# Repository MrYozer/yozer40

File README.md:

# yozer40
A 40% split space keyboard

Kicad design files, firmware coming later

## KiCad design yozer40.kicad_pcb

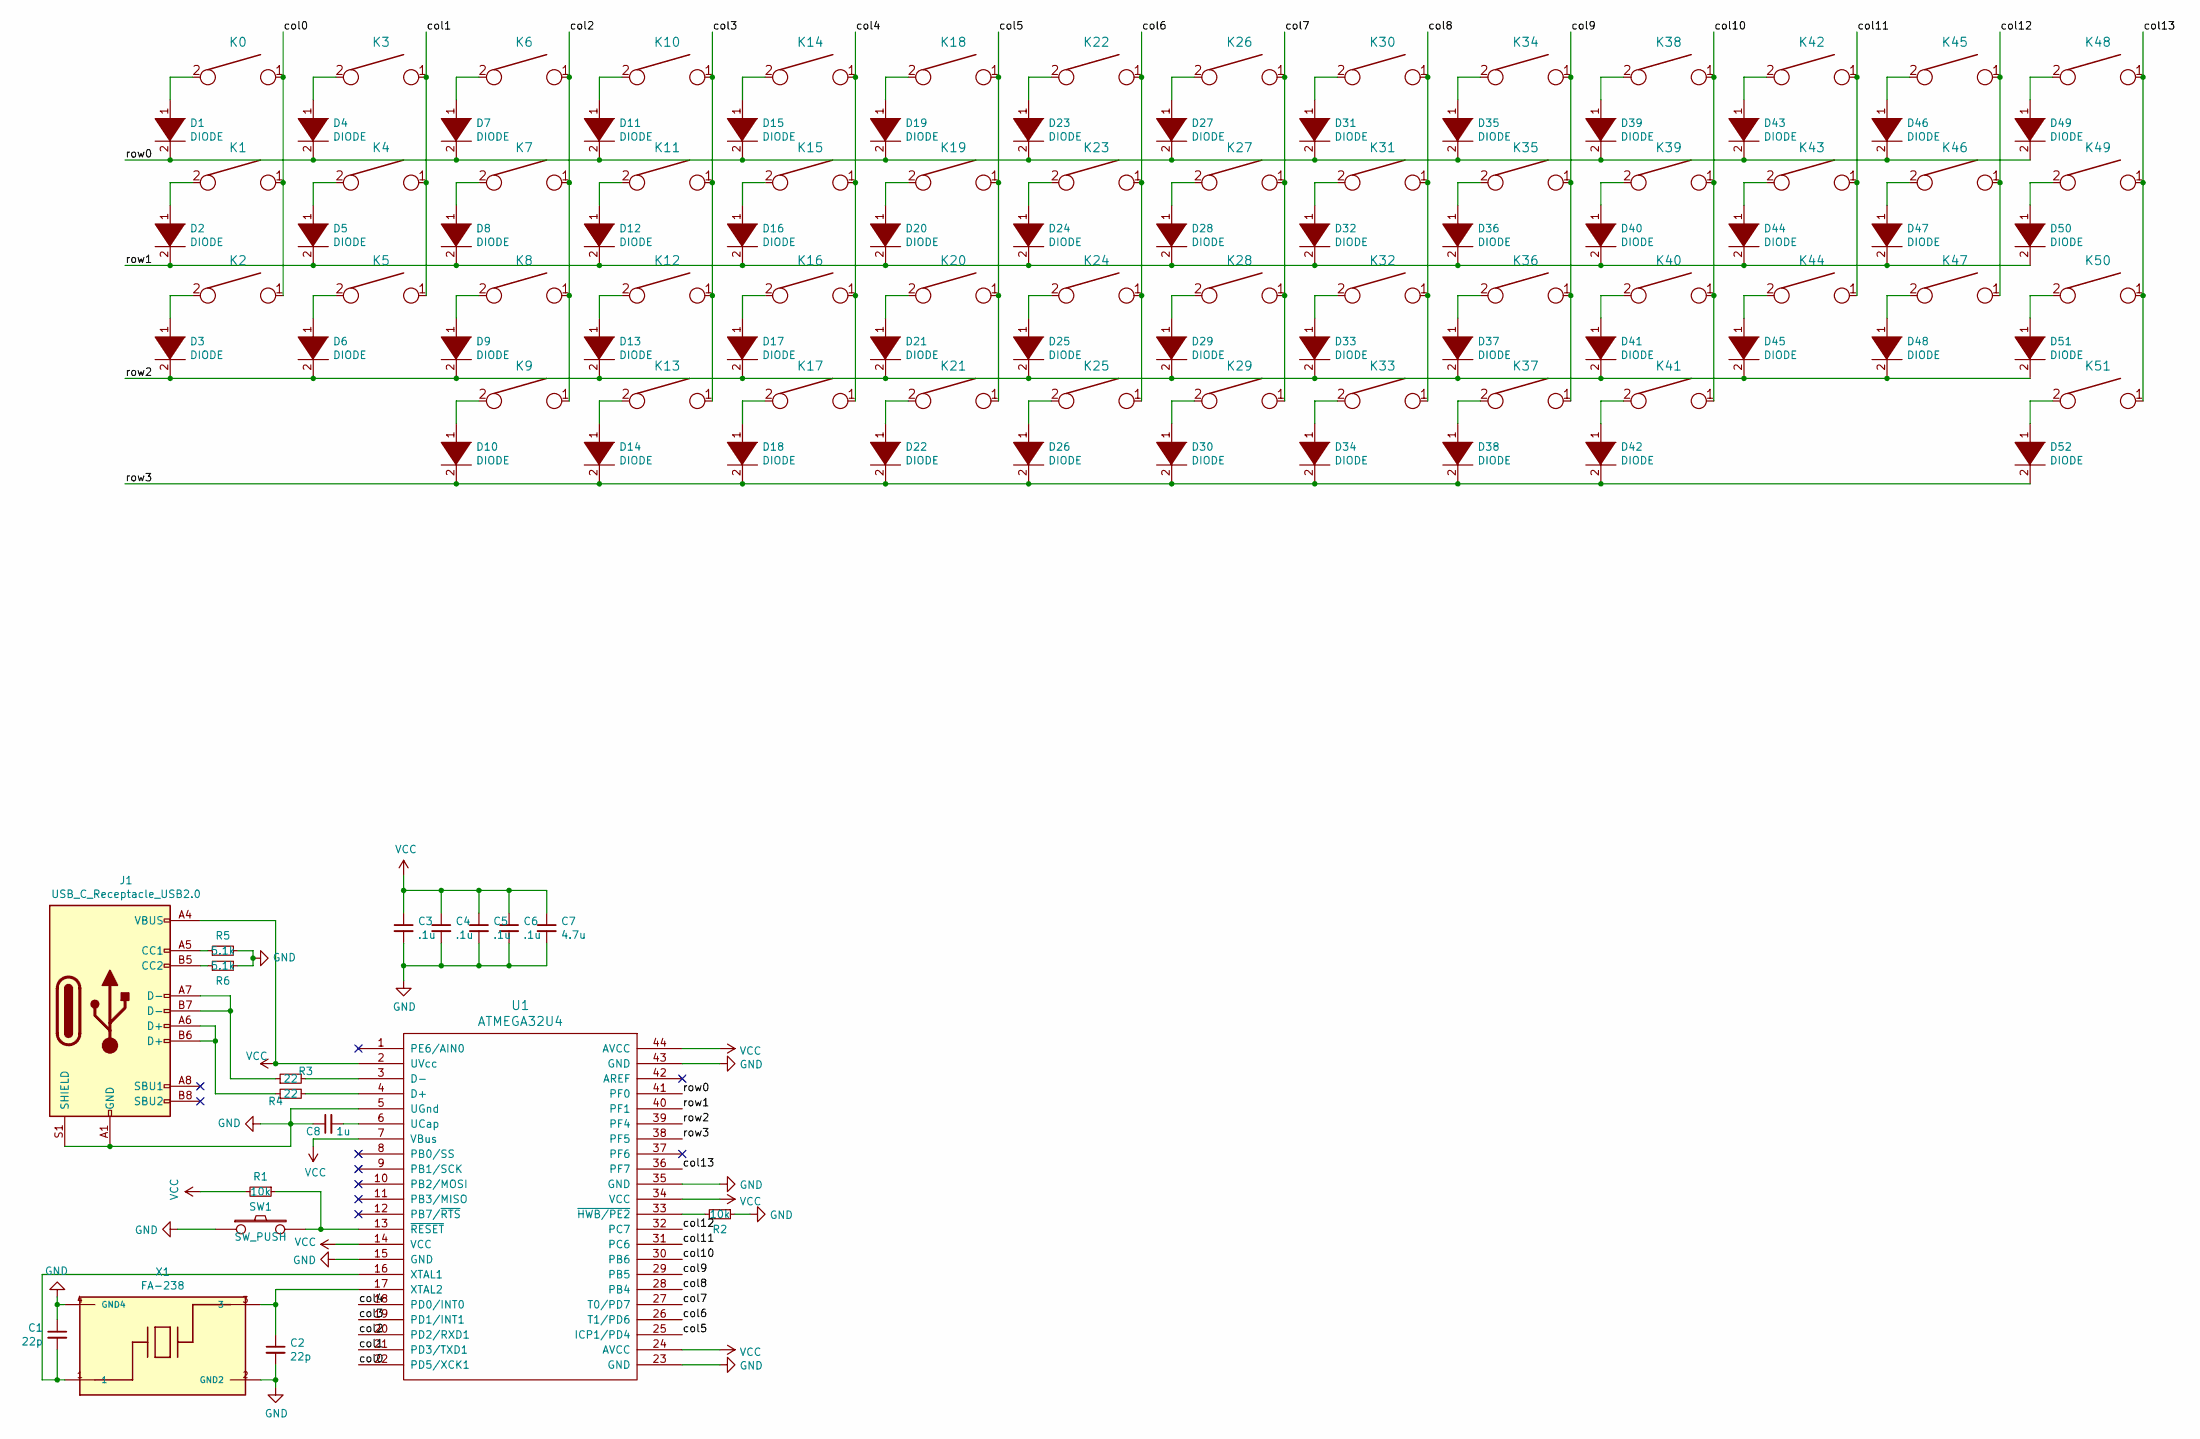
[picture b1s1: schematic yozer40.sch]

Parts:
C1, C2: 22p; C_0805_2012Metric_Pad1.18x1.45mm_HandSolder
C3, C4, C5, C6: .1u; C_0805_2012Metric_Pad1.18x1.45mm_HandSolder
C7: 4.7u; C_0805_2012Metric_Pad1.18x1.45mm_HandSolder
C8: 1u; C_0805_2012Metric_Pad1.18x1.45mm_HandSolder
D1, D2, D3, D4, D5, D6, D7, D8, D9, D10, D11, D12, D13, D14, D15, D16, D17, D18, D19, D20, D21, D22, D23, D24, D25, D26, D27, D28, D29, D30, D31, D32, D33, D34, D35, D36, D37, D38, D39, D40, D41, D42, D43, D44, D45, D46, D47, D48, D49, D50, D51, D52: DIODE; D_0805_2012Metric_Pad1.15x1.40mm_HandSolder
J1: USB_C_Receptacle_USB2.0; USB_C_Receptacle_GCT_USB4085
K0, K1, K2, K3, K6, K7, K8, K9, K10, K11, K12, K13, K14, K15, K16, K17, K18, K19, K20, K22, K23, K24, K25, K26, K27, K28, K30, K31, K32, K33, K34, K35, K36, K37, K38, K39, K40, K41, K42, K43, K44, K45, K46, K48, K50, K51: KEYSW; SW_Cherry_MX_1.00u_PCB
K4, K21, K29, K47: KEYSW; SW_Cherry_MX_1.25u_PCB
K5, K49: KEYSW; SW_Cherry_MX_1.75u_PCB
R1, R2: 10k; R_0805_2012Metric_Pad1.20x1.40mm_HandSolder
R3, R4: 22; R_0805_2012Metric_Pad1.20x1.40mm_HandSolder
R5, R6: 5.1k; R_0805_2012Metric_Pad1.20x1.40mm_HandSolder
SW1: SW_PUSH; SW_SPST_TL3342
U1: ATMEGA32U4; TQFP-44_10x10mm_P0.8mm
X1: FA-238; OSCCC320X250X70-4N

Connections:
/col0: K0.1, K1.1, K2.1, U1.22 (PD5/XCK1)
/col1: K3.1, K4.1, K5.1, U1.21 (PD3/TXD1)
/col2: K6.1, K7.1, K8.1, K9.1, U1.20 (PD2/RXD1)
/col3: K10.1, K11.1, K12.1, K13.1, U1.19 (PD1/INT1)
/col4: K14.1, K15.1, K16.1, K17.1, U1.18 (PD0/INT0)
/col5: K18.1, K19.1, K20.1, K21.1, U1.25 (ICP1/PD4)
/col6: K22.1, K23.1, K24.1, K25.1, U1.26 (T1/PD6)
/col7: K26.1, K27.1, K28.1, K29.1, U1.27 (T0/PD7)
/col8: K30.1, K31.1, K32.1, K33.1, U1.28 (PB4)
/col9: K34.1, K35.1, K36.1, K37.1, U1.29 (PB5)
/col10: K38.1, K39.1, K40.1, K41.1, U1.30 (PB6)
/col11: K42.1, K43.1, K44.1, U1.31 (PC6)
/col12: K45.1, K46.1, K47.1, U1.32 (PC7)
/col13: K48.1, K49.1, K50.1, K51.1, U1.36 (PF7)
/row0: D1.2 (A), D4.2 (A), D7.2 (A), D11.2 (A), D15.2 (A), D19.2 (A), D23.2 (A), D27.2 (A), D31.2 (A), D35.2 (A), D39.2 (A), D43.2 (A), D46.2 (A), D49.2 (A), U1.41 (PF0)
/row1: D2.2 (A), D5.2 (A), D8.2 (A), D12.2 (A), D16.2 (A), D20.2 (A), D24.2 (A), D28.2 (A), D32.2 (A), D36.2 (A), D40.2 (A), D44.2 (A), D47.2 (A), D50.2 (A), U1.40 (PF1)
/row2: D3.2 (A), D6.2 (A), D9.2 (A), D13.2 (A), D17.2 (A), D21.2 (A), D25.2 (A), D29.2 (A), D33.2 (A), D37.2 (A), D41.2 (A), D45.2 (A), D48.2 (A), D51.2 (A), U1.39 (PF4)
/row3: D10.2 (A), D14.2 (A), D18.2 (A), D22.2 (A), D26.2 (A), D30.2 (A), D34.2 (A), D38.2 (A), D42.2 (A), D52.2 (A), U1.38 (PF5)
GND: C1.1, C2.2, C3.2, C4.2, C5.2, C6.2, C7.2, C8.1, J1.A1 (GND), J1.A12 (GND), J1.B1 (GND), J1.B12 (GND), J1.S1 (SHIELD), R2.1, R5.2, R6.2, SW1.1, U1.5 (UGnd), U1.15 (GND), U1.23 (GND), U1.35 (GND), U1.43 (GND), X1.2 (GND2), X1.4 (GND4)
unnamed: C1.2, U1.16 (XTAL1), X1.1
unnamed: C2.1, U1.17 (XTAL2), X1.3
unnamed: C8.2, U1.6 (UCap)
unnamed: D1.1 (K), K0.2
unnamed: D2.1 (K), K1.2
unnamed: D3.1 (K), K2.2
unnamed: D4.1 (K), K3.2
unnamed: D5.1 (K), K4.2
unnamed: D6.1 (K), K5.2
unnamed: D7.1 (K), K6.2
unnamed: D8.1 (K), K7.2
unnamed: D9.1 (K), K8.2
unnamed: D10.1 (K), K9.2
unnamed: D11.1 (K), K10.2
unnamed: D12.1 (K), K11.2
unnamed: D13.1 (K), K12.2
unnamed: D14.1 (K), K13.2
unnamed: D15.1 (K), K14.2
unnamed: D16.1 (K), K15.2
unnamed: D17.1 (K), K16.2
unnamed: D18.1 (K), K17.2
unnamed: D19.1 (K), K18.2
unnamed: D20.1 (K), K19.2
unnamed: D21.1 (K), K20.2
unnamed: D22.1 (K), K21.2
unnamed: D23.1 (K), K22.2
unnamed: D24.1 (K), K23.2
unnamed: D25.1 (K), K24.2
unnamed: D26.1 (K), K25.2
unnamed: D27.1 (K), K26.2
unnamed: D28.1 (K), K27.2
unnamed: D29.1 (K), K28.2
unnamed: D30.1 (K), K29.2
unnamed: D31.1 (K), K30.2
unnamed: D32.1 (K), K31.2
unnamed: D33.1 (K), K32.2
unnamed: D34.1 (K), K33.2
unnamed: D35.1 (K), K34.2
unnamed: D36.1 (K), K35.2
unnamed: D37.1 (K), K36.2
unnamed: D38.1 (K), K37.2
unnamed: D39.1 (K), K38.2
unnamed: D40.1 (K), K39.2
unnamed: D41.1 (K), K40.2
unnamed: D42.1 (K), K41.2
unnamed: D43.1 (K), K42.2
unnamed: D44.1 (K), K43.2
unnamed: D45.1 (K), K44.2
unnamed: D46.1 (K), K45.2
unnamed: D47.1 (K), K46.2
unnamed: D48.1 (K), K47.2
unnamed: D49.1 (K), K48.2
unnamed: D50.1 (K), K49.2
unnamed: D51.1 (K), K50.2
unnamed: D52.1 (K), K51.2
unnamed: J1.A5 (CC1), R5.1
unnamed: J1.A6 (D+), J1.B6 (D+), R4.1
unnamed: J1.A7 (D-), J1.B7 (D-), R3.1
unnamed: J1.B5 (CC2), R6.1
unnamed: R1.1, SW1.2, U1.13 (~RESET)
unnamed: R2.2, U1.33 (~HWB/PE2)
unnamed: R3.2, U1.3 (D-)
unnamed: R4.2, U1.4 (D+)
VCC: C3.1, C4.1, C5.1, C6.1, C7.1, J1.A4 (VBUS), J1.A9 (VBUS), J1.B4 (VBUS), J1.B9 (VBUS), R1.2, U1.2 (UVcc), U1.7 (VBus), U1.14 (VCC), U1.24 (AVCC), U1.34 (VCC), U1.44 (AVCC)

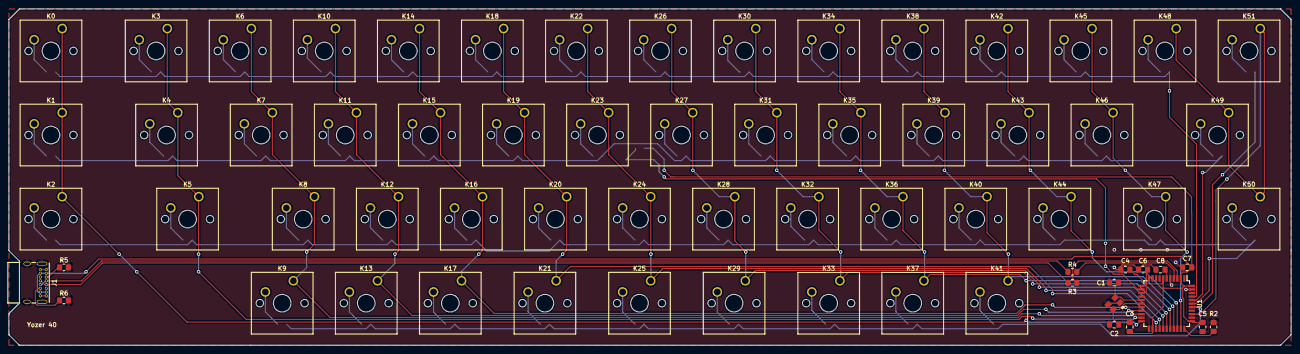
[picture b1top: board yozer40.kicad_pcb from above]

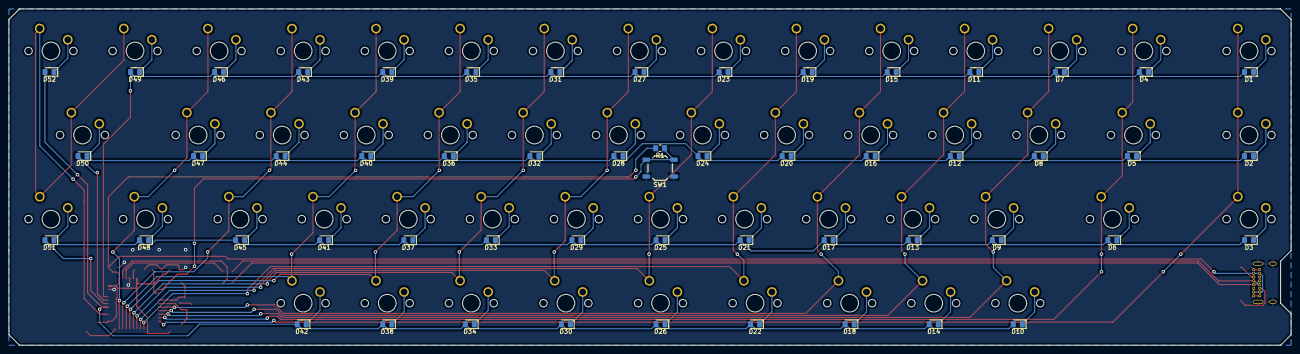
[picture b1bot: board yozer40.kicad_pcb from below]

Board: 2 copper layers, 290.5 x 76.2 mm, 122 parts (54 on the bottom side), 83 nets.

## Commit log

2021-07-10 added gitignore
2021-07-10 Create LICENSE
